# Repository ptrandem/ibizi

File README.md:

# iBizi

iBizi is a simple, color-based status indicator via a USB connection.

There are many other projects out there that have similar functionality, but none of them quite had the form factor we were looking for.

The iBizi project also aims to support the hardware with universal Chrome app support, making status changes a breeze.

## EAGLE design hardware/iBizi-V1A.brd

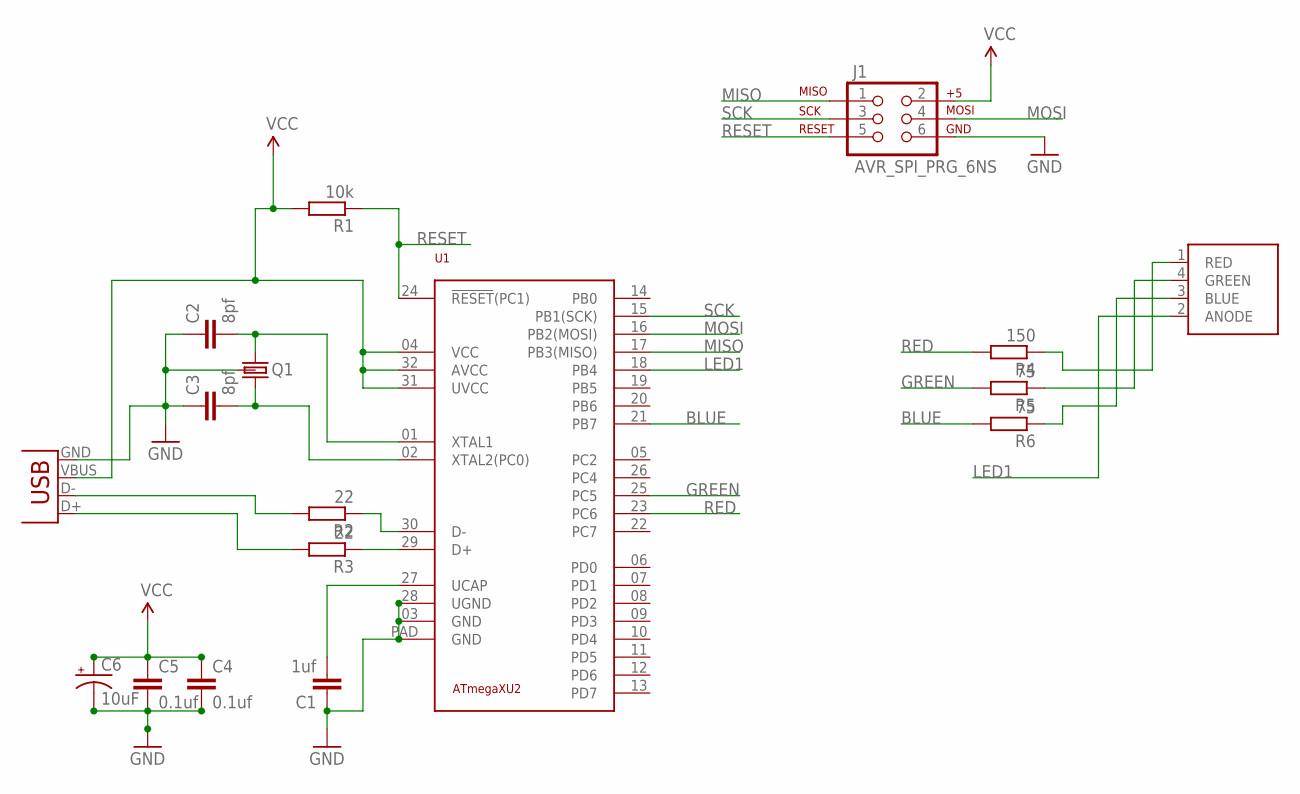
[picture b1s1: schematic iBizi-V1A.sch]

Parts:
C1: 1uf; C0402
C2, C3: 8pf; C0402
C4, C5: 0.1uf; C0402
C6: 10uF; EIA3216
J1: AVR_SPI_PRG_6NS; 2X3-NS
LED1: RGB-LED-CLV1A-FKB; PLCC4
Q1: CRYSTAL-EPSON-TSX3225-3.2X2.5; CRYSTAL-SMD-3.2X2.5
R1: 10k; R0402
R2, R3: 22; R0402
R4: 150; R0402
R5, R6: 75; R0402
U1: ATMEGAXU2; QFN32
USB: USBSMD; USB-MINIB

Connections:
BLUE: R6.2, U1.21 (PB7)
GND: C1.1, C2.1, C3.1, C4.2, C5.2, C6.C (-), J1.6, Q1.2 (GND), Q1.4 (GND), U1.03 (GND), U1.28 (UGND), U1.PAD (GND), USB.GND
GREEN: R5.2, U1.25 (PC5)
LED1: LED1.2 (ANODE), U1.18 (PB4)
MISO: J1.1, U1.17 (PB3(MISO))
MOSI: J1.4, U1.16 (PB2(MOSI))
unnamed: C2.2, Q1.1, U1.01 (XTAL1)
unnamed: C3.2, Q1.3 (2), U1.02 (XTAL2(PC0))
unnamed: R3.1, U1.29 (D+)
unnamed: R3.2, USB.D+
unnamed: R2.1, U1.30 (D-)
unnamed: R2.2, USB.D-
unnamed: LED1.1 (RED), R4.1
unnamed: LED1.4 (GREEN), R5.1
unnamed: LED1.3 (BLUE), R6.1
unnamed: C1.2, U1.27 (UCAP)
RED: R4.2, U1.23 (PC6)
RESET: J1.5, R1.1, U1.24 (!RESET!(PC1))
SCK: J1.3, U1.15 (PB1(SCK))
VCC: C4.1, C5.1, C6.A (+), J1.2, R1.2, U1.04 (VCC), U1.31 (UVCC), U1.32 (AVCC), USB.VBUS

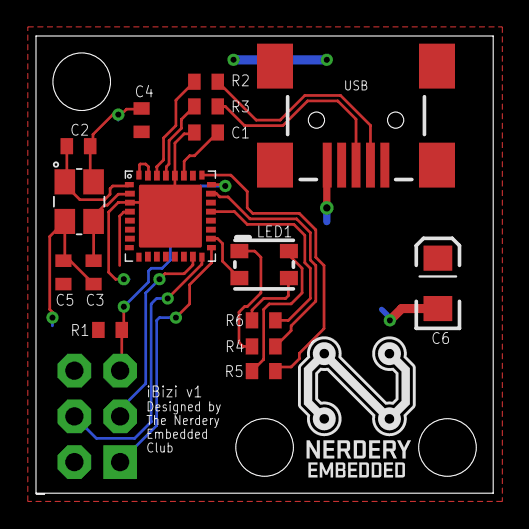
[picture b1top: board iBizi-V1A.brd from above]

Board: 2 copper layers, 25.4 x 25.4 mm, 17 parts (0 on the bottom side), 20 nets.

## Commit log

2015-03-31 adding hardware
2016-06-14 Adding licenses, some cleanup in prep for release
2016-06-14 name changes
2016-06-15 updating VID/PID with new pid.codes-provided code
2016-10-13 chrome app store changes
2016-10-13 app store changes
2016-10-13 hardware tweaks; outputs
2016-11-11 bliss
2016-11-11 disconnect no longer turns off light; minor tweaks, cleanup and upgrade to Atmel Studio 7ish
2016-11-11 adding production elf file for convenience
2016-11-11 updating versions and deployment
2016-11-11 adding windows test application to allow for testing many ibizis in a hot-swap situation (production line)
2018-03-06 stuff

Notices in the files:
parts and their libraries:
SparkFun-Connectors: Licensing: CC v3.0 Share-Alike You are welcome to use this library for commercial purposes.
